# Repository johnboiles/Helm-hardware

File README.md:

Helm
====
Board to convert RayMarine Seatalk to NMEA 0183 and vice versa. Also provides a connector for a TTL GPS such as SparkFun part #11571. I use it with a Raspberry PI connected over USB to get boat data into OpenCPN.

BOM
---
* 2x DS89C21 Differential CMOS Line Driver
* 1x Sparkfun Pro Micro 5V/16MHz
* 2x 12-pin female 100 mil headers
* 6x .1uF 0603 or 0805 capacitor
* 2x 4 connector 3.5mm screw terminal
* 1x 3 connector 3.5mm screw terminal
* 1x 2 connector 3.5mm screw terminal
* 3x 10k 0603 resistor
* 1x 15k 0603 resistor
* 1x 3.9k 0603 resistor
* 2x SOT-23 NPN transistor
* 1x EM406 (JST-SH) horizontal connector

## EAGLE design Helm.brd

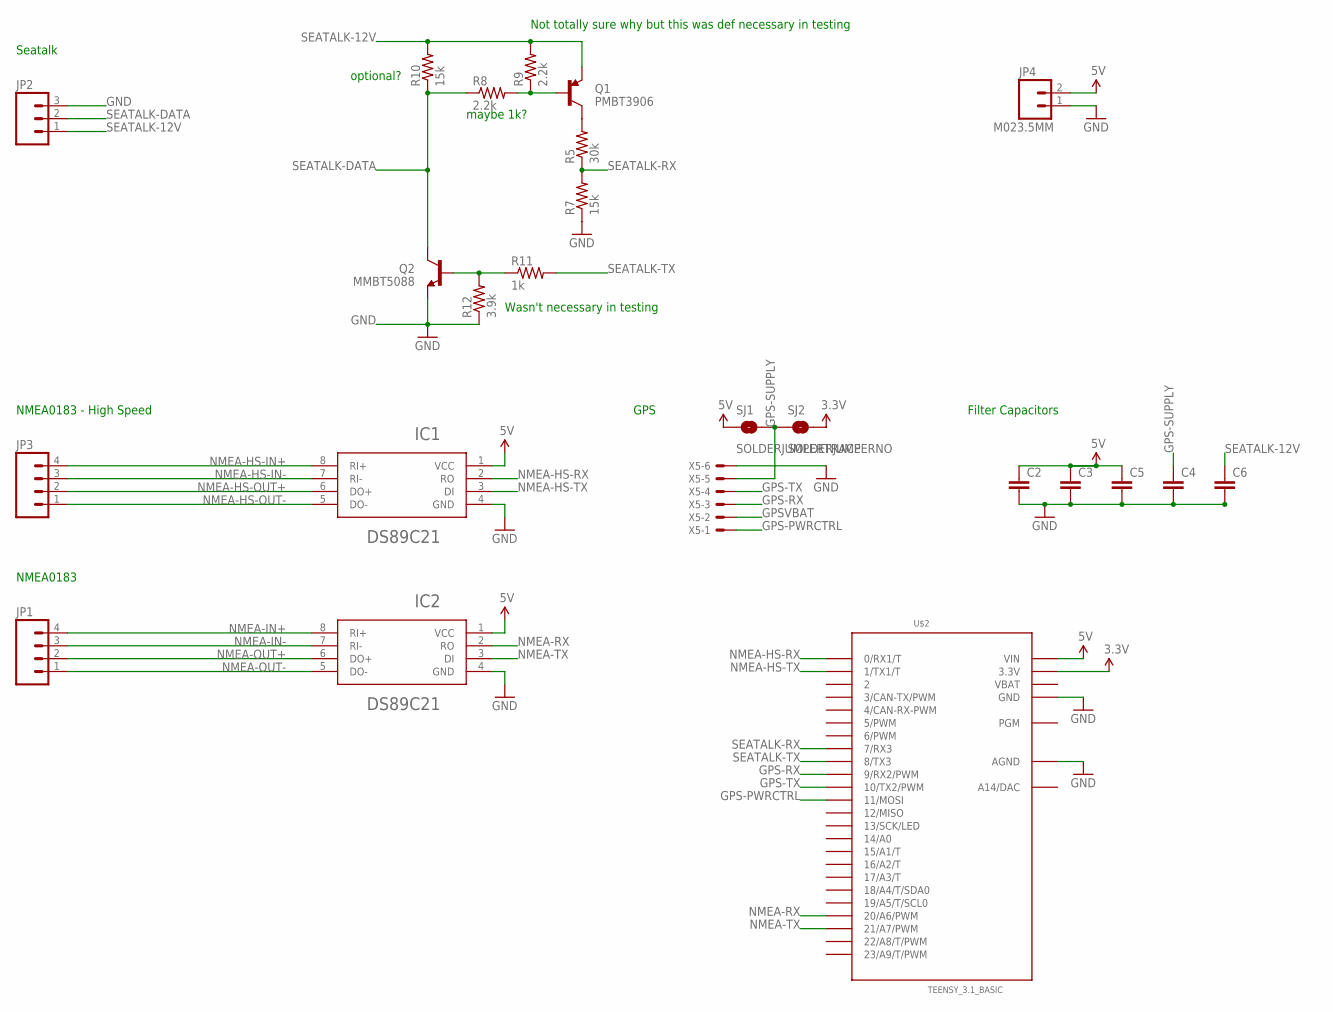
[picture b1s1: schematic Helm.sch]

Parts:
C2, C3, C4, C5, C6: CAP0805; 0805
IC1, IC2: DS89C21; SO08
JP1, JP3: M04SCREW; SCREWTERMINAL-3.5MM-4
JP2: M03SCREW; SCREWTERMINAL-3.5MM-3
JP4: M023.5MM; SCREWTERMINAL-3.5MM-2
Q1: PMBT3906; SOT23-3
Q2: MMBT5088; SOT23-3
R5: 30k; 0603-RES
R7, R10: 15k; 0603-RES
R8, R9: 2.2k; 0603-RES
R11: 1k; 0603-RES
R12: 3.9k; 0603-RES
SJ1: SOLDERJUMPERTRACE; SJ_2S-TRACE
SJ2: SOLDERJUMPERNO; SJ_2S-NO
U$2: TEENSY_3.1_BASIC
X5: SM06B-SRSS-TB

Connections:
3.3V: SJ2.2, U$2.3.3V, U$2.3.3V1 (3.3V)
5V: C2.1, C3.1, C5.1, IC1.1 (VCC), IC2.1 (VCC), JP4.2, SJ1.1, U$2.VIN
GND: C2.2, C3.2, C4.2, C5.2, C6.2, IC1.4 (GND), IC2.4 (GND), JP2.3, JP4.1, Q2.2 (E), R7.1, R12.1, U$2.AGND, U$2.GND, U$2.GND1 (GND), X5.6
GPS-PWRCTRL: U$2.11 (11/MOSI), X5.1
GPS-RX: U$2.9 (9/RX2/PWM), X5.3
GPS-SUPPLY: C4.1, SJ1.2, SJ2.1, X5.5
GPS-TX: U$2.10 (10/TX2/PWM), X5.4
GPSVBAT: X5.2
unnamed: Q1.3 (C), R5.2
unnamed: Q1.1 (B), R8.2, R9.1
unnamed: Q2.1 (B), R11.1, R12.2
NMEA-HS-IN+: IC1.8 (RI+), JP3.4
NMEA-HS-IN-: IC1.7 (RI-), JP3.3
NMEA-HS-OUT+: IC1.6 (DO+), JP3.2
NMEA-HS-OUT-: IC1.5 (DO-), JP3.1
NMEA-HS-RX: IC1.2 (RO), U$2.0 (0/RX1/T)
NMEA-HS-TX: IC1.3 (DI), U$2.1 (1/TX1/T)
NMEA-IN+: IC2.8 (RI+), JP1.4
NMEA-IN-: IC2.7 (RI-), JP1.3
NMEA-OUT+: IC2.6 (DO+), JP1.2
NMEA-OUT-: IC2.5 (DO-), JP1.1
NMEA-RX: IC2.2 (RO), U$2.20/A6 (20/A6/PWM)
NMEA-TX: IC2.3 (DI), U$2.21/A7 (21/A7/PWM)
SEATALK-12V: C6.1, JP2.1, Q1.2 (E), R9.2, R10.2
SEATALK-DATA: JP2.2, Q2.3 (C), R8.1, R10.1
SEATALK-RX: R5.1, R7.2, U$2.7 (7/RX3)
SEATALK-TX: R11.2, U$2.8 (8/TX3)
VBAT: U$2.VBAT

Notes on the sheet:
Seatalk
NMEA0183 - High Speed
GPS
NMEA0183
Filter Capacitors
optional?
maybe 1k?
Wasn't necessary in testing
Not totally sure why but this was def necessary in testing

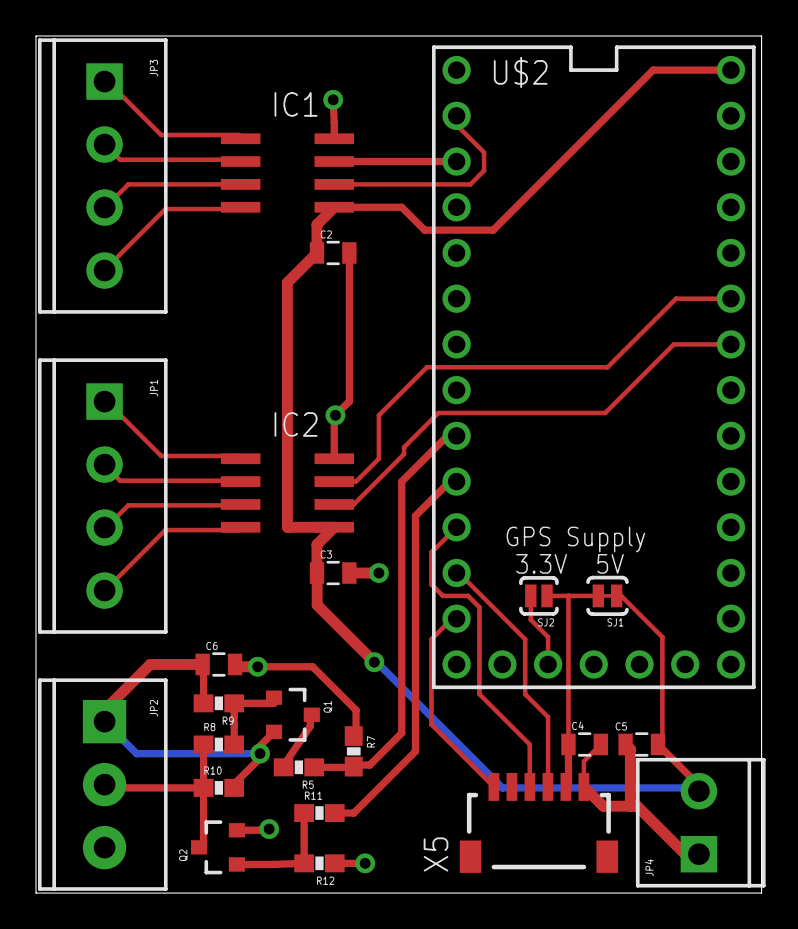
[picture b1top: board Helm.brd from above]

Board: 2 copper layers, 40.3 x 47.6 mm, 24 parts (0 on the bottom side), 26 nets.

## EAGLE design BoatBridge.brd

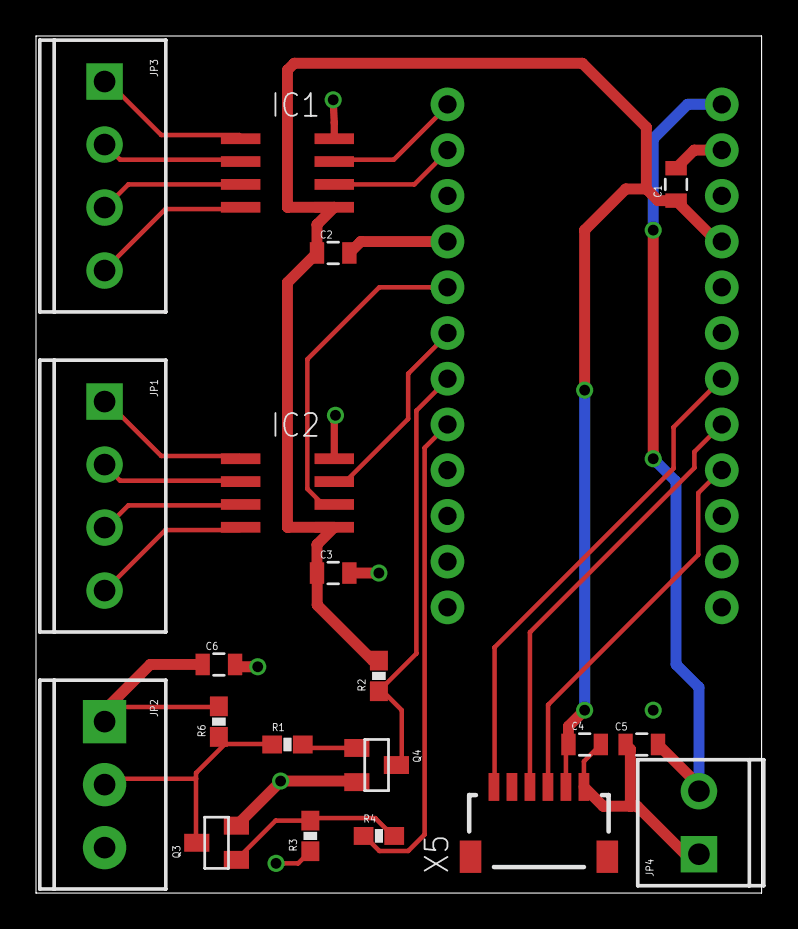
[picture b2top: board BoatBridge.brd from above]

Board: 2 copper layers, 40.3 x 47.6 mm, 21 parts (0 on the bottom side), 24 nets.

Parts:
C1, C2, C3, C4, C5, C6: 0805
IC1, IC2: DS89C21; SO08
JP1, JP3: SCREWTERMINAL-3.5MM-4
JP2: SCREWTERMINAL-3.5MM-3
JP4: M023.5MM; SCREWTERMINAL-3.5MM-2
Q3, Q4: SOT23
R1, R2, R4: 10k; 0603-RES
R3: 3.9k; 0603-RES
R6: 15k; 0603-RES
U$1: ARDUINO_PRO_MICRO
X5: SM06B-SRSS-TB

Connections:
5V: C1.1, C2.1, C3.1, C4.1, IC1.1, IC2.1, R2.2, U$1.21, X5.5
GND: C1.2, C2.2, C3.2, C4.2, C5.2, C6.2, IC1.4, IC2.4, JP2.3, JP4.1, Q3.2, Q4.2, R3.1, U$1.3, U$1.4, U$1.23, X5.6
GPS-PWRCTRL: U$1.18, X5.1
GPS-RX: U$1.17, X5.3
GPS-TX: U$1.16, X5.4
unnamed: Q4.1, R1.2
unnamed: Q3.1, R3.2, R4.2
NMEA-HS-IN+: IC1.8, JP3.4
NMEA-HS-IN-: IC1.7, JP3.3
NMEA-HS-OUT+: IC1.6, JP3.2
NMEA-HS-OUT-: IC1.5, JP3.1
NMEA-HS-RX: IC1.2, U$1.2
NMEA-HS-TX: IC1.3, U$1.1
NMEA-IN+: IC2.8, JP1.4
NMEA-IN-: IC2.7, JP1.3
NMEA-OUT+: IC2.6, JP1.2
NMEA-OUT-: IC2.5, JP1.1
NMEA-RX: IC2.2, U$1.5
NMEA-TX: IC2.3, U$1.6
SEATALK-12V: C6.1, JP2.1, R6.2
SEATALK-DATA: JP2.2, Q3.3, R1.1, R6.1
SEATALK-RX: Q4.3, R2.1, U$1.7
SEATALK-TX: R4.1, U$1.8
VRAW: C5.1, JP4.2, U$1.24

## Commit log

2014-10-13 Initial commit -- v1 of board to interface with SeaTalk and NMEA0183
2015-04-12 Rename to Helm
2015-04-12 WIP on v2 of the board
2017-06-09 v2 of the board. Now using Teensy3.1 for more hardware serial ports.

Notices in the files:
parts and their libraries:
SparkFun-Connectors: Licensing: Creative Commons ShareAlike 4.0 International - https://creativecommons.org/licenses/by-sa/4.0
